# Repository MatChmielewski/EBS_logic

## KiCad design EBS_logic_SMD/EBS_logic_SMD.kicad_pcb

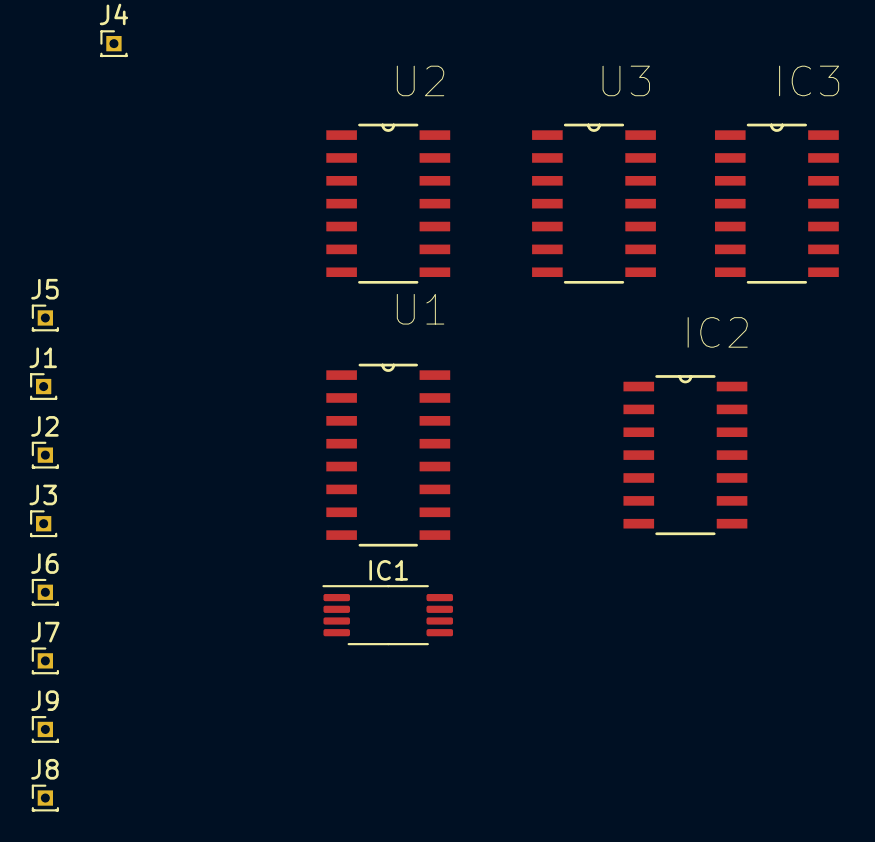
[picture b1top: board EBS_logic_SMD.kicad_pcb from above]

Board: 2 copper layers, 15 parts (0 on the bottom side), 20 nets, no tracks yet.

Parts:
IC1: UCC2946PW; TSSOP-8_4.4x3mm_P0.65mm
IC2: SN74HC08D; SOIC127P600X175-14N
IC3: SN74HC32D; SOIC127P600X175-14N
J1: AS_driving_mode; PinHeader_1x01_P1.00mm_Vertical
J2: TS_Activation_Button cockpit; PinHeader_1x01_P1.00mm_Vertical
J3: TS_Activation_Button external; PinHeader_1x01_P1.00mm_Vertical
J4: VCC; PinHeader_1x01_P1.00mm_Vertical
J5: AS_close_SDC; PinHeader_1x01_P1.00mm_Vertical
J6: Watchdog; PinHeader_1x01_P1.00mm_Vertical
J7: Shutdown_circuit; PinHeader_1x01_P1.00mm_Vertical
J8: SDC_is_ready; PinHeader_1x01_P1.00mm_Vertical
J9: To_SDC_relais; PinHeader_1x01_P1.00mm_Vertical
U1: 74HC157D,653; SOIC127P600X175-16N
U2: 74HC00D,653; SOIC127P600X175-14N
U3: MM74HC74AM; SOIC127P600X175-14N

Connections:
unnamed: IC1.3, U3.7, U3.10
unnamed: IC1.5, IC2.1
unnamed: IC1.7, J6.1
unnamed: IC1.8, IC2.14, IC3.14, J4.1, U1.16, U2.14, U3.14
unnamed: IC2.2, J7.1
unnamed: IC2.4, U3.3
unnamed: IC2.5, IC2.9, U3.9
unnamed: IC2.6, J9.1
unnamed: IC2.8, J8.1
unnamed: IC2.3, IC2.10, IC3.2
unnamed: IC3.1, U3.2
unnamed: IC3.3, U3.13
unnamed: J1.1, U1.1
unnamed: J2.1, U1.2
unnamed: J3.1, U1.3
unnamed: J5.1, U2.1
unnamed: U1.4, U2.2
unnamed: U2.3, U3.4
unnamed: U3.5, U3.6
unnamed: U3.11, U3.12

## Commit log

2021-02-09 Add STM code
